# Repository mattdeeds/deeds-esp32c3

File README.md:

# Deeds ESP32-C3
A slim ESP32-C3 development board with the option of programming over an USB-C cable or USB-A dongle

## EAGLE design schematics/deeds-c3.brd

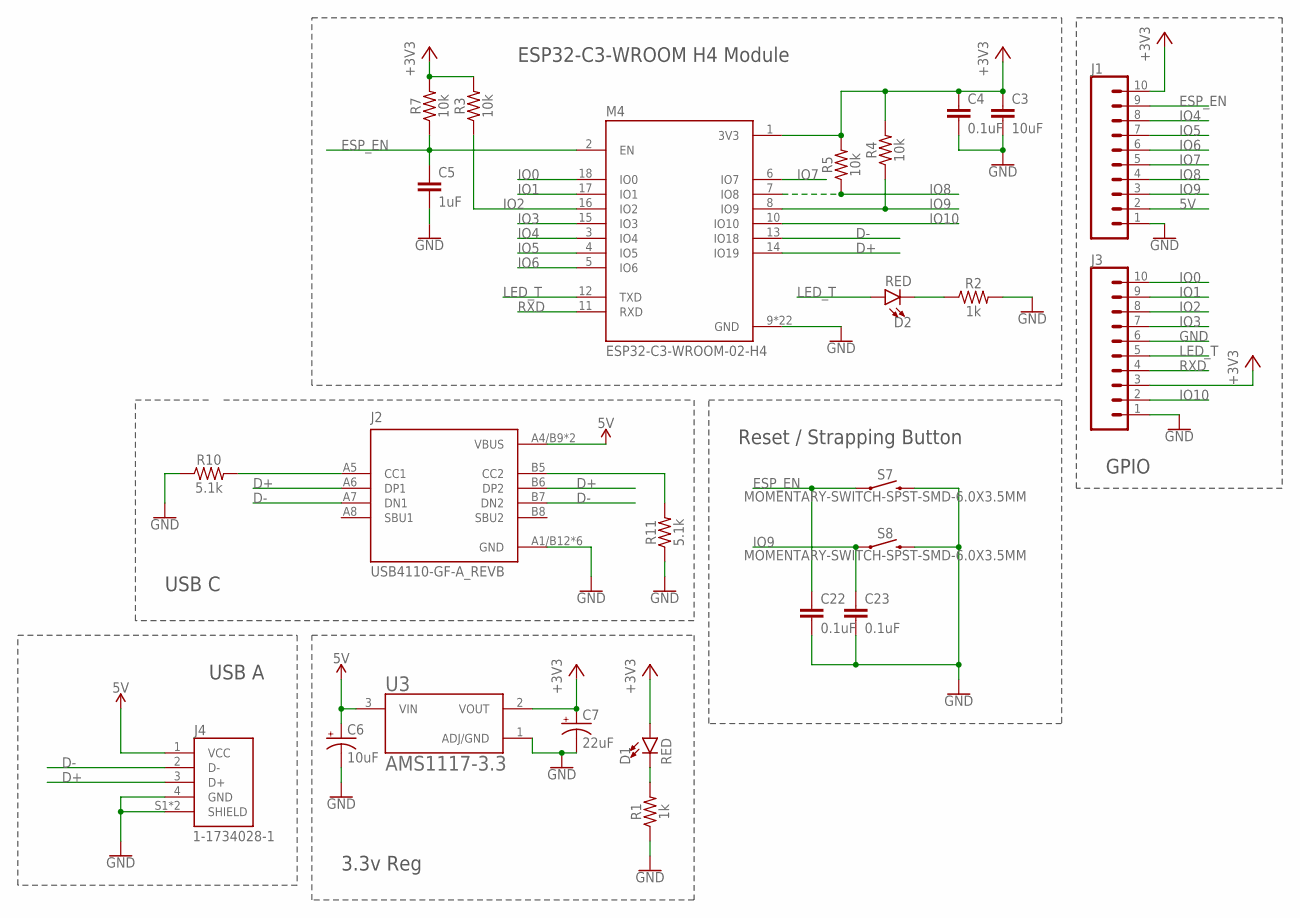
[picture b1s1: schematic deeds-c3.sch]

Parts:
C3: 10uF; 0603
C4, C22, C23: 0.1uF; 0603
C5: 1uF; 0603
C6: 10uF; EIA3216
C7: 22uF; EIA3216
D1, D2: RED; LED-0603
J1, J3: CONN_10"; 1X10
J2: USB4110-GF-A_REVB; GCT_USB4110-GF-A_REVB
J4: 1-1734028-1; TE_1-1734028-1
M4: ESP32-C3-WROOM-02-H4; MODULE_ESP32-C3-WROOM-02-H4
R1, R2: 1k; 0603
R3, R4, R5, R7: 10k; 0603
R10, R11: 5.1k; 0603
S7, S8: MOMENTARY-SWITCH-SPST-SMD-6.0X3.5MM; TACTILE_SWITCH_SMD_6.0X3.5MM
U3: AMS1117-3.3; SOT229P700X180-4N

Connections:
5V: C6.+, J1.2, J2.A4/B9 (VBUS), J2.B4/A9 (VBUS), J4.1 (VCC), U3.3 (VIN)
+3V3: C3.1, C4.1, C7.+, D1.A, J1.10, J3.3, M4.1 (3V3), R3.2, R4.2, R5.2, R7.2, U3.2 (VOUT)
D+: J2.A6 (DP1), J2.B6 (DP2), J4.3 (D+), M4.14 (IO19)
D-: J2.A7 (DN1), J2.B7 (DN2), J4.2 (D-), M4.13 (IO18)
ESP_EN: C5.1, C22.1, J1.9, M4.2 (EN), R7.1, S7.1
GND: C3.2, C4.2, C5.2, C6.-, C7.-, C22.2, C23.2, J1.1, J2.A1/B12 (GND), J2.B1/A12 (GND), J2.S1 (GND), J2.S2 (GND), J2.S3 (GND), J2.S4 (GND), J3.1, J3.6, J4.4 (GND), J4.S1 (SHIELD), J4.S2 (SHIELD), M4.9 (GND), M4.19 (GND), M4.20 (GND), M4.21 (GND), M4.22 (GND), M4.23 (GND), M4.24 (GND), M4.25 (GND), M4.26 (GND), M4.27 (GND), M4.28 (GND), M4.29 (GND), M4.30 (GND), M4.31 (GND), M4.32 (GND), M4.33 (GND), M4.34 (GND), M4.35 (GND), M4.36 (GND), M4.37 (GND), M4.38 (GND), M4.39 (GND), R1.1, R2.2, R10.1, R11.1, S7.2, S8.2, U3.1 (ADJ/GND)
IO0: J3.10, M4.18 (IO0)
IO1: J3.9, M4.17 (IO1)
IO2: J3.8, M4.16 (IO2), R3.1
IO3: J3.7, M4.15 (IO3)
IO4: J1.8, M4.3 (IO4)
IO5: J1.7, M4.4 (IO5)
IO6: J1.6, M4.5 (IO6)
IO7: J1.5, M4.6 (IO7)
IO8: J1.4, M4.7 (IO8), R5.1
IO9: C23.1, J1.3, M4.8 (IO9), R4.1, S8.1
IO10: J3.2, M4.10 (IO10)
LED_T: D2.A, J3.5, M4.12 (TXD)
unnamed: D2.C, R2.1
unnamed: D1.C, R1.2
unnamed: J2.A5 (CC1), R10.2
unnamed: J2.B5 (CC2), R11.2
RXD: J3.4, M4.11 (RXD)

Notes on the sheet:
ESP32-C3-WROOM H4 Module
Reset / Strapping Button
USB A
3.3v Reg
USB C
GPIO

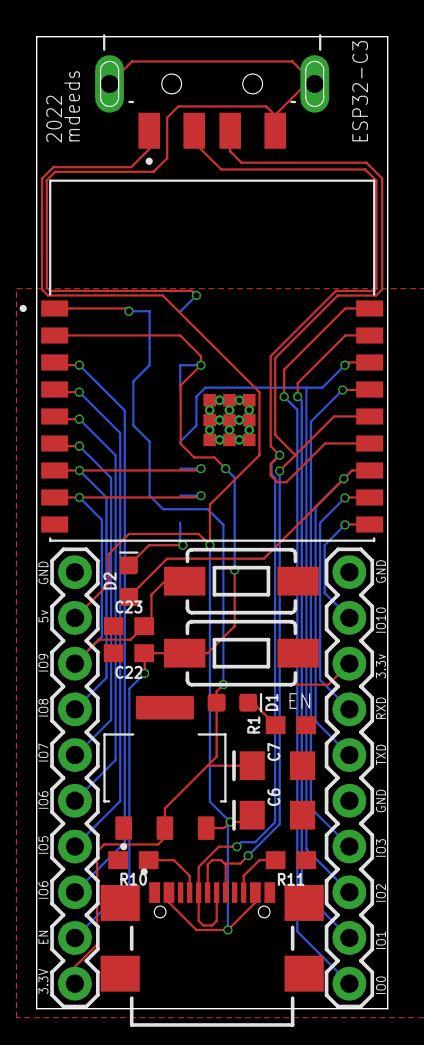
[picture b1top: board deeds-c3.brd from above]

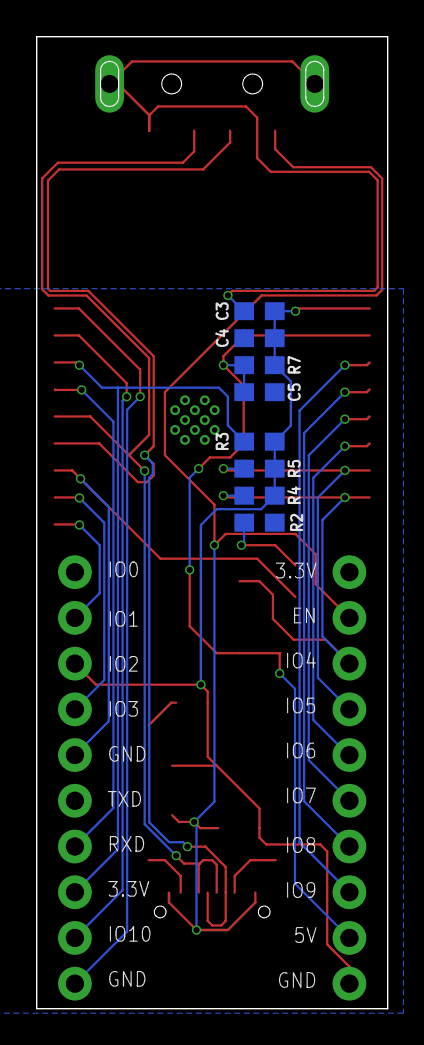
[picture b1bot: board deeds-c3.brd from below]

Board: 2 copper layers, 19.5 x 54.0 mm, 25 parts (8 on the bottom side), 23 nets.

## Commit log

2022-10-16 update images

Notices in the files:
parts and their libraries:
SparkFun-Capacitors: Licensing: Creative Commons ShareAlike 4.0 International - https://creativecommons.org/licenses/by-sa/4.0
